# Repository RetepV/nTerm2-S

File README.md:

# nTerm2-S

> [!IMPORTANT]
> I have permanently decided to drop the CP2102 in favor of the FT231 as a USB<->Serial bridge. The CP2102 is just near impossible to solder with a soldering iron, and it was one of my objectives to not have to use hot air. As the rest of the design design is basically still the same, I decided to freeze this repository, keeping it like it is for whoever is interested, and start a new repository for the FT231 version. The design is working: if you make a board it should work, mine does.\
> \
> However, do note that I decided to move to the FT231 already before I made boards with the ESD USB protection circuit USBLC6-2SC6. It's in the latest design files here, but no boards were made and it has not been tested. However, that circuit is so uncomplicated, that I'm sure it will work fine. In worst case you can leave out the USBLC6-2SC6 and just connect pins 1-6 and 3-4. However, without ESD protection, I would suggest to connect the nTerm2-S through a cheap USB hub. No sense in jeopardising your USB ports.\
> \
> Also, I decided to add an RTC to nTerm2-S, and that's only in the FT231 version.\
> \
> Long story short, have look here for continuation of this project: https://github.com/RetepV/nTerm2-S-FT231

My rendition of the uTerm2-S by Just4Fun (https://hackaday.io/project/181583-uterm2-s-a-multi-emulation-color-rs232-terminal). This one is in SMD, and I hopefully made it easily hand-solderable for everyone (with maybe the exception of the CP2102). Obviously the 'n' in nTerm stands for 'nano.' :P

The nTerm2-S has a slightly more usable form the uTerm2-S, I think. Smaller and a little more usable when sitting permanently on a desk. And as an extra, it can switch between normal and cross (null-modem) from the software so that you wil never have to search for that null-modem cable ever again. It can also switch between RTS/CTS or DTR/DSR handshaking.

Supports RxD/TxD with RTS/CTS. Also supports DTR/DSR in a way. It is possible to switch the RTS/CTS lines to the DTR/DSR lines, using the ESP32's RTS/CTS support to manage the DTR/DSR. It's not really DTR/DSR, but as the ESP32 is a plenty fast enough DTE and only the DCE might be slow, it will work most of the times.

The nTerm2-S is ultimately based on the FABGL library and board design from Fabrizio Di Vittori. http://www.fabglib.org. However, I skipped Fabrizio's implementation and based my design on Just4Fun's uTerm2-S. https://j4f.info/uterm2-s

THIS IS A WORK IN PROGESS! I.E. UNLESS STATED AS WORKING, ASSUME THAT IT DOES NOT WORK! NO FIRMWARE HAS BEEN TESTED YET, AND AS THERE ARE SMALL DIFFERENCES IN GPIO ASSIGNMENTS, I DON'T EXPECT THE DEFAULT FABGL EXAMPLES TO WORK WITHOUT TWEAKS.

<sub><s>NOTE: The relay circuit with the bistable relays is directly out of the OMRON databook, and it allows me to switch the relay but use only power when switching (and some losses through the 470 resistor when switched on: 7mA continuous, which is a huge of a lot better than 30mA continuous when using a normal relay). That circuit sources the power from the input, which is connected to a GPIO. ESP32 GPIO pins can source 40mA and sink 28mA. According to the datasheet, the relay needs 100mW of power to switch. At 3V, that is 33mA, but we use 3.3V, so some 30mA. So when switching 'on', the ESP32 will need to source 30mA and settle at some 7mA (all theoretically, be advised). That is quite a lot, but still within spec. The ESP32 does not have to sink much, as the reverse current will go through the diode directly to ground.</s><sub>

<sub>It turned out that the ESP32 was not able to source enough power after all, so I have had to change the circuit somewhat. Now all the necessary power comes from the 5V Vbus and is switched through another transistor. I couldn't properly measure the current draw from the ESP32's GPIO port, but it looked as if it was some 4mA.</sub>

<sub>Progress! I received my fuses and did some real measurements. I used 3.3V, BAT45 (commit says 1N4148, but I was mistaken, they are BAT45's), BC337, 220u and 470 ohm on my bread board, and measured about 14mA max when switching, and 6.8mA continuous. I expected more than 14mA when switching, but maybe this relay is better than the specs? In any case, I decided to experiment with the C and R. I upped the C to 470uF, which seemed to make the switching more reliable. But more importantly, I increased the resistor in steps to see what the result would be. And found that I could go up to at least 3K9 before the switching would become unreliable. 10K was clearly too much, and I didn't try anything in between 3K9 and 10K. With 3K9, 0.88mA is drawn, and I find that good enough. The low current power led uses 3mA, and I keep that on all the time. 1mA is fine.</sub>

<sub>Created the gerbers for v0.1 and sent out to JLPCB. Jeez, it's cheap. 11 euro for 5 boards. Still had a bunch of warnings from the pins/vias of the USB-C connector and ESP32 footprints that I just could not resolve. Decided to take my chances, and JLCPCB accepted the gerbers and has actually already finished and posted the boards. So I expect the boards to be here in a few days. In the mean time, I've been doing some basic work and redesign for a version 2 of the nTerm2-S, with an SD card slot and psram, to make it more versatile (e.g. PC emulation). However, let's get this first version to work first, the objective is to have a terminal with software switchable null-modem.</sub>

<sub>After my v0.1 boards arrived I built one up. I did it in stages, starting with the CP2102 and then the power (I use the CP2102 in bus-powered mode). After much cursing, I got the CP2012 straight on the pads and it looked good under the microscope. I then added the power supply components and the USB-C port. No ESD protection yet. Doublechecked everything 10 times under the microscope, got out an old cheap USB hub (better to blow up the hub than my Macbook's port) and plugged the nTerm in. And Windows detected the CP2102 immediately, installed the drivers, and... success #1 was there!</sub>

<sub>I then added the ESP32. Could update its firmware. Success #2! Soldered the video DAC and VGA port (and fixed the ESP32). Success #3: we have video! Then populated the keyboard and mouse circuits. Success #4! After playing some Space Invaders, I populated the MAX3232 and hardwired the Rx and Tx together to do a loopback test. And we had success #5!</sub>

<sub>Then the problems started. After populating the relay circuits, I could not get them to switch. After lots of measuring and experimenting with an oscilloscope, I could only conclude that the ESP32 was simply not able to source a high enough voltage and that all my calculations and experiments apparently had been wrong. The switching voltage of the relay is 3V. But I found that the ESP32, in my setting, delivered only some 3.15V, and that goes through the BAT43W diode. The diode has a low voltage drop, but it's still something like 0.55V or more at 30mA, and that brings the operating voltage down to 2.61V. Switching one way (with a 1 on the GPIO), it means that the relay gets 2.61V, which is enough to switch it that way. But not the other way. The capacitor is charged with 2.61V. But when it discharges, it discharges through the BC817, which adds another voltage drop of somewhere between 0.1 and 0.4 volt. And now, with worst case 2.21V we are just around the minimum set voltage for the relay, which is 2.25V typical. The charge in the capacitor is not enough to deliver enough energy in that case.</sub>

<sub>So now I had to experiment with the board itself and found that what I could do was to change the input diode to a transistor in common collector (emitter follower) configuration, and basically buffer ESP32's GPIO. So I replaced the BAT43 diode with a BC817 transistor, with collector tied to 5V and emitter tied to the input of the circuit. This brings the voltage into the circuit up to the 3.15V that the ESP32 was outputting (voltage drop of the transistor is negated by feeding it 5V). And after fiddling a bit with resistor and capacitor values I got it all working reliably.</sub>

<sub>I left it at that, it was working now with minimal changes and no inrease in cost.</sub>

<sub>Problems encountered and fixed:</sub>

<sub>1. The CP2102 was really hard to solder, even using hot air. I am looking into the FT231 as a much easier to solder alternative. But the FT231 seems to have more driver issues than the CP2102 (which has none, as far as I know). As an alternative, it might help to increase the size of the pads.
2. The ESD protection diodes were much tinier than I thought. Looking at the PCB in Kicad, they didn't seem so small. :) So I should try to find larger diodes.
3. I thought I had an ESP32 lying around, but it turned out that I only had one that was soldered to a breakout board. So I decided to desolder that, instead of wait for new ones to arrive. Well, that did not go too well. I ripped off one of the castellated pads, one which is used for hSync. So no video. But I a not defeated so easily, so I lifted the cap off the module, soldered a wire directly to the ESP32 chip and ran it to the HSYNC line. Win! .;) I could start some serious testing
4. The relay circuits don't work. Had to redesign somewhat.
5. I accidentally used the J-leg footprint for the IM41's instead of the Gullwing footprint.
6. Many of the large capacitor's footprints were simply wrong and I had to solder one vertically.
7. I used tantalum caps in the relay circuits, but there's no reason to not use the much cheaper normal electrolytic caps.
</sub>

<sub>After a fixing all of the above, and refactoring a few things on the board, version v0.6 was arrived at. And once again I had boards made by JCPCB. 17 euro for 5 boards. Still cheap, but no discount for me this time. The new boards arrived in record time, and I went to populate one.<s/ub>

<sub>Observations:</sub>

<sub>1. Still have one capacitor's footprint wrong. Although this I was able to fit it horizontally at least.
2. CP2102 solders much easier with the larger sized pads. But it still is fiddly to hand-solder a QFN-28 chip. I wish Silicon Labs would make a QFP-28 version.
3. The board is detected by my Macbook, but can't communicate with it. My Windows machine is luckily able to communicate and flash, but it doesn't seem too happy about it all. What's going on? Turns out that I had chosen ESD diodes for their size, but did not realize that with their size also comes a high capacity of some 100pF. And that's enough to mess up the USB communications. So it's back to the ol' drawing board here. Removing the ESD diodes makes USB work again on all my machines. But i want them, so we'll need a new revision already. 
4. My new relay circuits work! Flawlessly even!
5. Why did I not add an option to keep the amplifier circuit unpopulated and have a line-out instead of a speaker-out? Or why not both options, selectable throguh solder bridges?</sub>

<sub>Apart from these issues, nTerm2-S v0.5 works!</sub>

<sub>v0.1 vs v0.5:</sub>

<sub>Testing v0.5</sub>

<sub>I just finished the v0.6 design with fixes for all of the above. That would be the final design, with only a slight feature creep (being able to omit/bypass the speaker amplifier). Now we need software...</sub>

This design is available under GPL License V3. This means that I DO NOT release it for commercial use, unless with my explicit written and signed consent. Please contact me if you have commercial questions.

uTerm2-S: https://hackaday.io/project/181583-uterm2-s-a-multi-emulation-color-rs232-terminal  
fabgl: http://www.fabglib.org/, https://github.com/fdivitto/FabGL

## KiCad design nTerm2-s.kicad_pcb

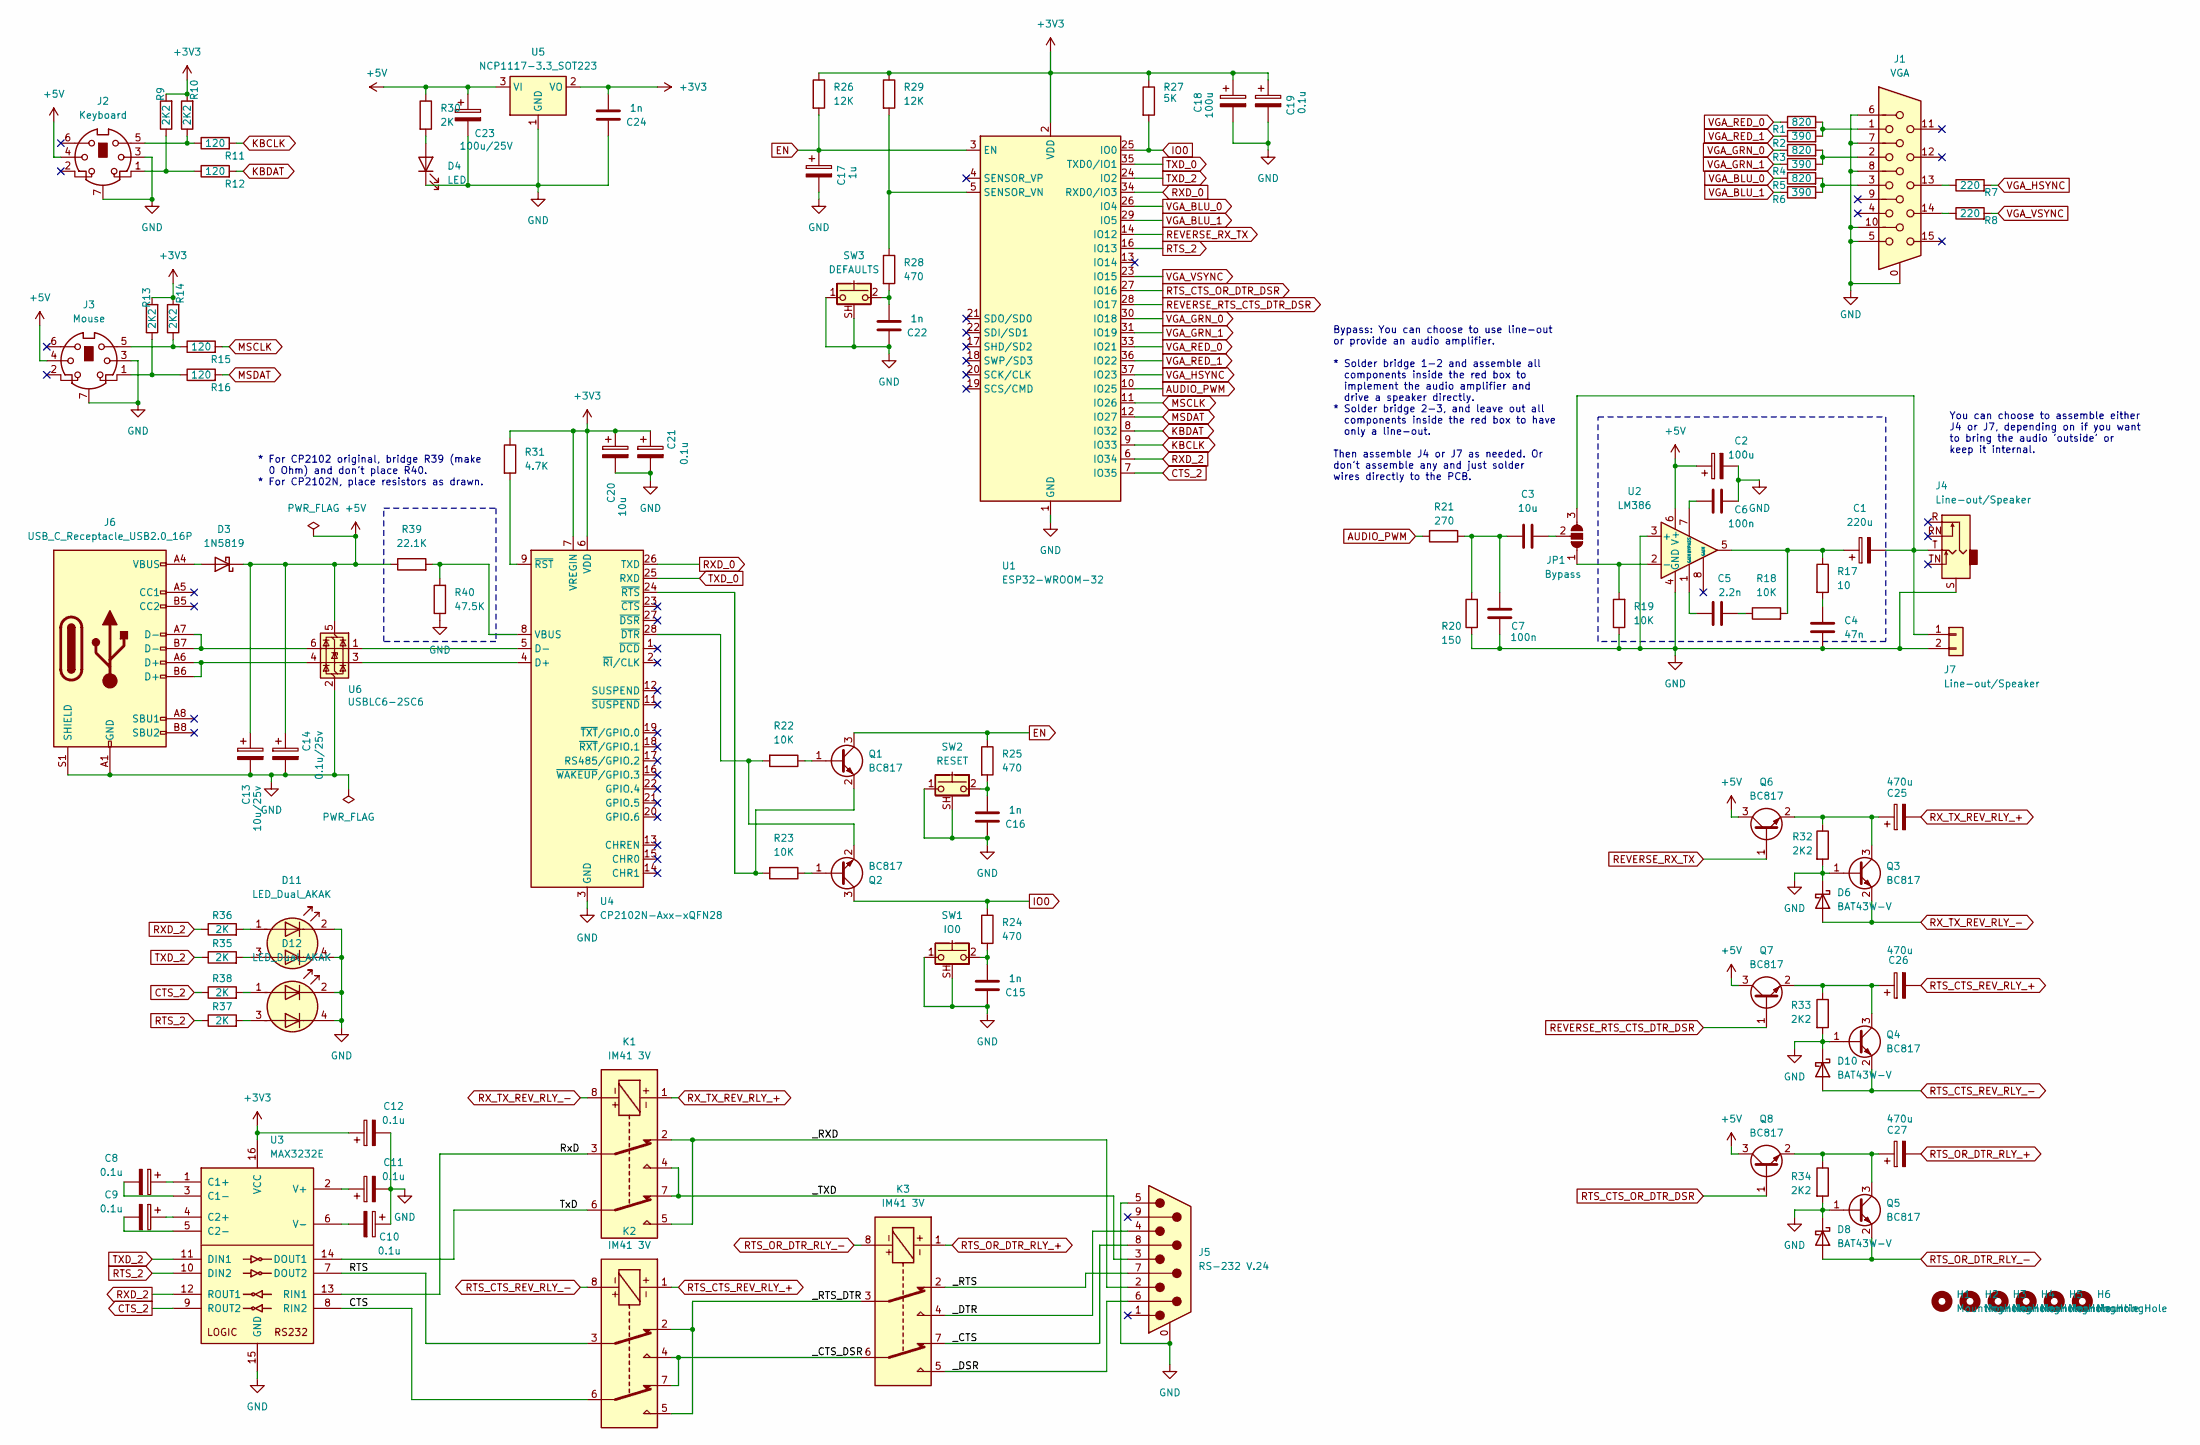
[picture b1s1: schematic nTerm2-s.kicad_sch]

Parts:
C1: 220u; CP_Elec_6.3x7.7
C2: 100u; CP_Elec_6.3x7.7
C3: 10u; C_0805_2012Metric_Pad1.18x1.45mm_HandSolder
C4: 47n; C_0603_1608Metric_Pad1.08x0.95mm_HandSolder
C5: 2.2n; C_0603_1608Metric_Pad1.08x0.95mm_HandSolder
C6, C7: 100n; C_0603_1608Metric_Pad1.08x0.95mm_HandSolder
C8, C9, C10, C11, C12, C19, C21: 0.1u; CP_EIA-3216-18_Kemet-A_Pad1.58x1.35mm_HandSolder
C13: 10u/25v; CP_EIA-6032-28_Kemet-C_Pad2.25x2.35mm_HandSolder
C14: 0.1u/25v; CP_EIA-3216-18_Kemet-A_Pad1.58x1.35mm_HandSolder
C15, C16, C22, C24: 1n; C_0603_1608Metric_Pad1.08x0.95mm_HandSolder
C17: 1u; CP_EIA-3216-18_Kemet-A_Pad1.58x1.35mm_HandSolder
C18: 100u; CP_EIA-6032-28_Kemet-C_Pad2.25x2.35mm_HandSolder
C20: 10u; CP_EIA-3528-21_Kemet-B_Pad1.50x2.35mm_HandSolder
C23: 100u/25V; CP_EIA-7343-30_AVX-N_Pad2.25x2.55mm_HandSolder
C25, C26, C27: 470u; CP_Elec_6.3x7.7
D3: 1N5819; Nexperia_CFP3_SOD-123W
D4: LED; DIALIGHT_LED_3MM_SINGLE
D6, D8, D10: BAT43W-V; D_SOD-123
D11, D12: LED_Dual_AKAK; DIALIGHT_LED_3MM_DOUBLE
H1, H2, H3, H4, H5, H6: MountingHole; MountingHole_3.2mm_M3
J1: VGA; DSUB-15-HD_Female_Horizontal_P2.29x1.98mm_EdgePinOffset3.03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
J2: Keyboard; Connector_Mini-DIN_Female_6Pin_2rows
J3: Mouse; Connector_Mini-DIN_Female_6Pin_2rows
J4: Line-out/Speaker; Jack_3.5mm_Ledino_KB3SPRS_Horizontal-alt
J5: RS-232 V.24; DSUB-9_Male_Horizontal_P2.77x2.84mm_EdgePinOffset4.94mm_Hou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
J6: USB_C_Receptacle_USB2.0_16P; USB_C_Receptacle_Molex_213716-0001
J7: Line-out/Speaker; PinHeader_1x02_P2.54mm_Vertical
JP1: Bypass; SolderJumper-3_P1.3mm_Open_RoundedPad1.0x1.5mm_NumberLabels
K1, K2, K3: IM41 3V; Relay_DPDT_AXICOM_IMSeries_Gullwing
Q1, Q2, Q3, Q4, Q5, Q6, Q7, Q8: BC817; SOT-23
R1, R3, R5: 820; R_0603_1608Metric_Pad0.98x0.95mm_HandSolder
R2, R4, R6: 390; R_0603_1608Metric_Pad0.98x0.95mm_HandSolder
R7, R8: 220; R_0603_1608Metric_Pad0.98x0.95mm_HandSolder
R9, R10, R13, R14, R32, R33, R34: 2K2; R_0603_1608Metric_Pad0.98x0.95mm_HandSolder
R11, R12, R15, R16: 120; R_0603_1608Metric_Pad0.98x0.95mm_HandSolder
R17: 10; R_0603_1608Metric_Pad0.98x0.95mm_HandSolder
R18, R19, R22, R23: 10K; R_0603_1608Metric_Pad0.98x0.95mm_HandSolder
R20: 150; R_0603_1608Metric_Pad0.98x0.95mm_HandSolder
R21: 270; R_0603_1608Metric_Pad0.98x0.95mm_HandSolder
R24, R25, R28: 470; R_0603_1608Metric_Pad0.98x0.95mm_HandSolder
R26, R29: 12K; R_0603_1608Metric_Pad0.98x0.95mm_HandSolder
R27: 5K; R_0603_1608Metric_Pad0.98x0.95mm_HandSolder
R30, R35, R36, R37, R38: 2K; R_0603_1608Metric_Pad0.98x0.95mm_HandSolder
R31: 4.7K; R_0603_1608Metric_Pad0.98x0.95mm_HandSolder
R39: 22.1K; R_0603_1608Metric_Pad0.98x0.95mm_HandSolder
R40: 47.5K; R_0603_1608Metric_Pad0.98x0.95mm_HandSolder
SW1: IO0; SW_Tactile_SPST_Angled_PTS645Vx58-2LFS-alt
SW2: RESET; SW_Tactile_SPST_Angled_PTS645Vx58-2LFS-alt
SW3: DEFAULTS; SW_Tactile_SPST_Angled_PTS645Vx58-2LFS-alt
U1: ESP32-WROOM-32
U2: LM386; SOIC-8_3.9x4.9mm_P1.27mm
U3: MAX3232E; SOIC-16_3.9x9.9mm_P1.27mm
U4: CP2102N-Axx-xQFN28; QFN-28-1EP_5x5mm_P0.5mm_EP3.35x3.35mm_handsolder
U5: NCP1117-3.3_SOT223; SOT-223-3_TabPin2
U6: USBLC6-2SC6; SOT-23-6

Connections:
+3V3: C12.1, C18.1, C19.1, C20.1, C21.1, C24.1, R9.2, R10.2, R13.2, R14.2, R26.1, R27.1, R29.1, R31.1, U1.2 (VDD), U3.16 (VCC), U4.6 (VDD), U4.7 (VREGIN), U5.2 (VO)
+5V: C2.1, C13.1, C14.1, C23.1, D3.1 (K), J2.4, J3.4, Q6.3 (C), Q7.3 (C), Q8.3 (C), R30.1, R39.1, U2.6 (V+), U5.3 (VI), U6.5 (VBUS)
/CTS: K2.6, U3.8 (RIN2)
/RTS: K2.3, U3.7 (DOUT2)
/RxD: K1.3, U3.13 (RIN1)
/TxD: K1.6, U3.14 (DOUT1)
/_CTS: J5.8, K3.7
/_CTS_DSR: K2.4, K2.7, K3.6
/_DSR: J5.6, K3.5
/_DTR: J5.4, K3.4
/_RTS: J5.7, K3.2
/_RTS_DTR: K2.2, K2.5, K3.3
/_RXD: J5.2, K1.2, K1.5
/_TXD: J5.3, K1.4, K1.7
AUDIO_PWM: R21.2, U1.10 (IO25)
CTS_2: R38.1, U1.7 (IO35), U3.9 (ROUT2)
EN: C17.1, Q1.3 (C), R25.1, R26.2, U1.3 (EN)
GND: C2.2, C4.2, C6.2, C7.1, C10.1, C11.2, C12.2, C13.2, C14.2, C15.2, C16.2, C17.2, C18.2, C19.2, C20.2, C21.2, C22.2, C23.2, C24.2, D4.2 (K), D6.1 (K), D8.1 (K), D10.1 (K), D11.2 (K1), D11.4 (K2), D12.2 (K1), D12.4 (K2), J1.0, J1.5, J1.6, J1.7, J1.8, J1.10, J2.3, J2.7, J3.3, J3.7, J4.S, J5.0 (PAD), J5.5, J6.A1 (GND), J6.A12 (GND), J6.B1 (GND), J6.B12 (GND), J6.S1 (SHIELD), J7.2, Q3.1 (B), Q4.1 (B), Q5.1 (B), R19.1, R20.1, R32.2, R33.2, R34.2, R40.1, SW1.1, SW1.SH (B), SW2.1, SW2.SH (B), SW3.1, SW3.SH (B), U1.1 (GND), U1.15 (GND), U1.38 (GND), U1.39 (GND), U2.3 (+), U2.4 (GND), U3.15 (GND), U4.3 (GND), U4.29 (GND), U5.1 (GND), U6.2 (GND)
IO0: Q2.3 (C), R24.1, R27.2, U1.25 (IO0)
KBCLK: R11.2, U1.9 (IO33)
KBDAT: R12.2, U1.8 (IO32)
MSCLK: R15.2, U1.11 (IO26)
MSDAT: R16.2, U1.12 (IO27)
unnamed: C1.1, R17.1, R18.2, U2.5
unnamed: C3.1, C7.2, R20.2, R21.1
unnamed: C4.1, R17.2
unnamed: C5.1, U2.1 (GAIN)
unnamed: C5.2, R18.1
unnamed: C15.1, R24.2, SW1.2
unnamed: C16.1, R25.2, SW2.2
unnamed: C22.1, R28.2, SW3.2
unnamed: D3.2 (A), J6.A4 (VBUS), J6.A9 (VBUS), J6.B4 (VBUS), J6.B9 (VBUS)
unnamed: D4.1 (A), R30.2
unnamed: D11.1 (A1), R36.2
unnamed: D11.3 (A2), R35.2
unnamed: D12.1 (A1), R38.2
unnamed: D12.3 (A2), R37.2
unnamed: J1.1, R1.2, R2.2
unnamed: J1.2, R3.2, R4.2
unnamed: J1.3, R5.2, R6.2
unnamed: J1.13, R7.1
unnamed: J1.14, R8.1
unnamed: J2.1, R9.1, R12.1
unnamed: J2.5, R10.1, R11.1
unnamed: J3.1, R13.1, R16.1
unnamed: J3.5, R14.1, R15.1
unnamed: J6.A6 (D+), J6.B6 (D+), U6.4 (I/O2)
unnamed: J6.A7 (D-), J6.B7 (D-), U6.6 (I/O1)
unnamed: C1.2, J4.T, J7.1, JP1.3 (B)
unnamed: JP1.1 (A), R19.2, U2.2 (-)
unnamed: C3.2, JP1.2 (C)
unnamed: Q1.1 (B), R22.1
unnamed: Q1.2 (E), R23.2, U4.24 (~RTS)
unnamed: Q2.1 (B), R23.1
unnamed: Q2.2 (E), R22.2, U4.28 (~DTR)
unnamed: C25.1, Q3.3 (C), Q6.2 (E), R32.1
unnamed: C26.1, Q4.3 (C), Q7.2 (E), R33.1
unnamed: C27.1, Q5.3 (C), Q8.2 (E), R34.1
unnamed: R28.1, R29.2, U1.5 (SENSOR_VN)
unnamed: C6.1, U2.7 (BYPASS)
unnamed: C8.1, U3.1 (C1+)
unnamed: C8.2, U3.3 (C1-)
unnamed: C9.1, U3.4 (C2+)
unnamed: C9.2, U3.5 (C2-)
unnamed: C11.1, U3.2 (V+)
unnamed: C10.2, U3.6 (V-)
unnamed: U4.4 (D+), U6.3 (I/O2)
unnamed: U4.5 (D-), U6.1 (I/O1)
unnamed: R39.2, R40.2, U4.8 (VBUS)
unnamed: R31.2, U4.9 (~RST)
REVERSE_RTS_CTS_DTR_DSR: Q7.1 (B), U1.28 (IO17)
REVERSE_RX_TX: Q6.1 (B), U1.14 (IO12)
RTS_2: R37.1, U1.16 (IO13), U3.10 (DIN2)
RTS_CTS_OR_DTR_DSR: Q8.1 (B), U1.27 (IO16)
RTS_CTS_REV_RLY_+: C26.2, K2.1
RTS_CTS_REV_RLY_-: D10.2 (A), K2.8, Q4.2 (E)
RTS_OR_DTR_RLY_+: C27.2, K3.1
RTS_OR_DTR_RLY_-: D8.2 (A), K3.8, Q5.2 (E)
RXD_0: U1.34 (RXD0/IO3), U4.26 (TXD)
RXD_2: R36.1, U1.6 (IO34), U3.12 (ROUT1)
RX_TX_REV_RLY_+: C25.2, K1.1
RX_TX_REV_RLY_-: D6.2 (A), K1.8, Q3.2 (E)
TXD_0: U1.35 (TXD0/IO1), U4.25 (RXD)
TXD_2: R35.1, U1.24 (IO2), U3.11 (DIN1)
VGA_BLU_0: R5.1, U1.26 (IO4)
VGA_BLU_1: R6.1, U1.29 (IO5)
VGA_GRN_0: R3.1, U1.30 (IO18)
VGA_GRN_1: R4.1, U1.31 (IO19)
VGA_HSYNC: R7.2, U1.37 (IO23)
VGA_RED_0: R1.1, U1.33 (IO21)
VGA_RED_1: R2.1, U1.36 (IO22)
VGA_VSYNC: R8.2, U1.23 (IO15)

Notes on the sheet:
You can choose to assemble either J4 or J7, depending on if you want to bring the audio 'outside' or keep it internal.
* For CP2102 original, bridge R39 (make 0 Ohm) and don't place R40. * For CP2102N, place resistors as drawn.
Bypass: You can choose to use line-out or provide an audio amplifier. * Solder bridge 1-2 and assemble all components inside the red box to implement the audio amplifier and drive a speaker directly. * Solder bridge 2-3, and leave out all components inside the red box to have only a line-out. Then 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

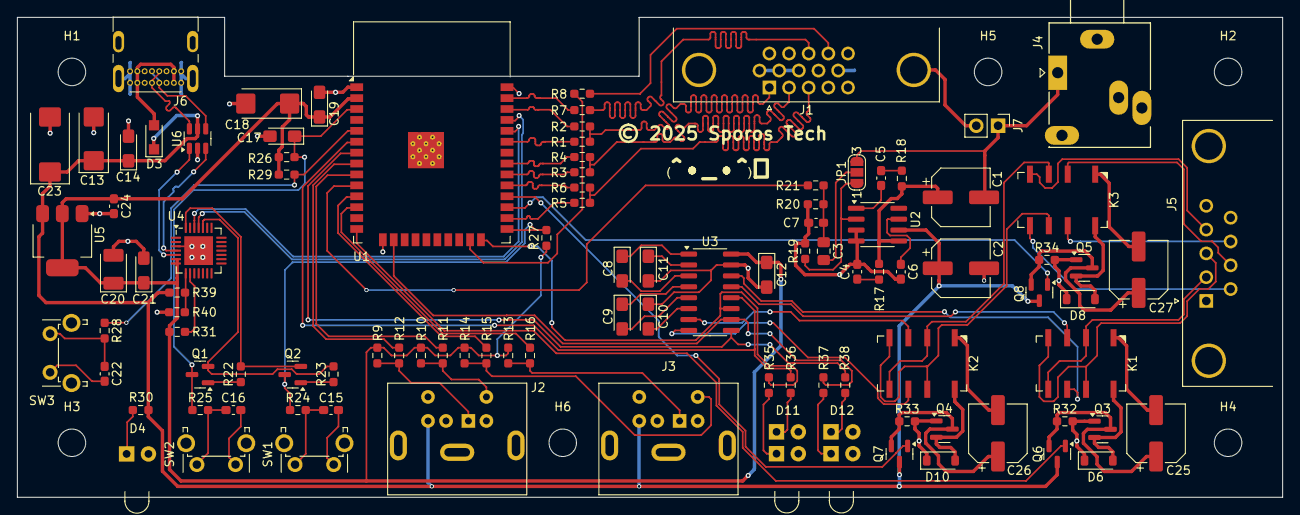
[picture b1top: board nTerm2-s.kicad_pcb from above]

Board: 2 copper layers, 147.3 x 55.9 mm, 108 parts (0 on the bottom side), 92 nets.

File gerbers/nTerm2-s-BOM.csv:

"Id";"Designator";"Footprint";"Quantity";"Designation";"Supplier and ref";
1;"R28,R25,R24";"R_0603_1608Metric_Pad0.98x0.95mm_HandSolder";3;"470";;;
2;"R2,R4,R6";"R_0603_1608Metric_Pad0.98x0.95mm_HandSolder";3;"390";;;
3;"R26,R29";"R_0603_1608Metric_Pad0.98x0.95mm_HandSolder";2;"12K";;;
4;"R33,R34,R32";"R_0603_1608Metric_Pad0.98x0.95mm_HandSolder";3;"3K9";;;
5;"R18,R22,R23,R19";"R_0603_1608Metric_Pad0.98x0.95mm_HandSolder";4;"10K";;;
6;"D1,D2";"D_SMA";2;"P4SMAJ5.0CA";;;
7;"D7,D10,D5,D9,D6,D8";"D_SOD-123";6;"BAT43W-V";;;
8;"K1,K2,K3";"Relay_DPDT_AXICOM_IMSeries_Gullwing";3;"IM41 3V";;;
9;"SW2";"SW_Tactile_SPST_Angled_PTS645Vx58-2LFS";1;"RESET";;;
10;"R17";"R_0603_1608Metric_Pad0.98x0.95mm_HandSolder";1;"10";;;
11;"U1";"ESP32-WROOM-32";1;"ESP32-WROOM-32";;;
12;"R14,R9,R13,R10";"R_0603_1608Metric_Pad0.98x0.95mm_HandSolder";4;"2K2";;;
13;"SW1";"SW_Tactile_SPST_Angled_PTS645Vx58-2LFS";1;"IO0";;;
14;"C6,C7";"C_0603_1608Metric_Pad1.08x0.95mm_HandSolder";2;"100n";;;
15;"J2";"Connector_Mini-DIN_Female_6Pin_2rows";1;"Keyboard";;;
16;"C25,C26,C27";"CP_Elec_6.3x7.7";3;"470u";;;
17;"D11,D12";"DIALIGHT_LED_3MM_DOUBLE";2;"LED_Dual_AKAK";;;
18;"R38,R37,R36,R35,R30";"R_0603_1608Metric_Pad0.98x0.95mm_HandSolder";5;"2K";;;
19;"U2";"SOIC-8_3.9x4.9mm_P1.27mm";1;"LM386";;;
20;"R8,R7";"R_0603_1608Metric_Pad0.98x0.95mm_HandSolder";2;"220";;;
21;"C24,C16,C15,C22";"C_0603_1608Metric_Pad1.08x0.95mm_HandSolder";4;"1n";;;
22;"R12,R15,R16,R11";"R_0603_1608Metric_Pad0.98x0.95mm_HandSolder";4;"120";;;
23;"C10,C9,C21,C12,C8,C11,C19";"CP_EIA-3216-18_Kemet-A_Pad1.58x1.35mm_HandSolder";7;"0.1u";;;
24;"C14";"CP_EIA-3216-18_Kemet-A_Pad1.58x1.35mm_HandSolder";1;"0.1u/25v";;;
25;"J3";"Connector_Mini-DIN_Female_6Pin_2rows";1;"Mouse";;;
26;"U5";"SOT-223-3_TabPin2";1;"NCP1117-3.3_SOT223";;;
27;"C18";"CP_EIA-6032-28_Kemet-C_Pad2.25x2.35mm_HandSolder";1;"100u";;;
28;"R20";"R_0603_1608Metric_Pad0.98x0.95mm_HandSolder";1;"150";;;
29;"U3";"SOIC-16_3.9x9.9mm_P1.27mm";1;"MAX3232E";;;
30;"C23";"CP_EIA-6032-28_Kemet-C_Pad2.25x2.35mm_HandSolder";1;"100u/25V";;;
31;"Q5,Q2,Q1,Q3,Q4";"SOT-23";5;"BC817";;;
32;"R39";"R_0603_1608Metric_Pad0.98x0.95mm_HandSolder";1;"22.1K";;;
33;"J6";"USB_C_Receptacle_Molex_213716-0001";1;"USB_C_Receptacle_USB2.0_16P";;;
34;"C20";"CP_EIA-3528-21_Kemet-B_Pad1.50x2.35mm_HandSolder";1;"10u";;;
35;"SW3";"SW_Tactile_SPST_Angled_PTS645Vx58-2LFS";1;"DEFAULTS";;;
36;"C5";"C_0603_1608Metric_Pad1.08x0.95mm_HandSolder";1;"2.2n";;;
37;"R5,R3,R1";"R_0603_1608Metric_Pad0.98x0.95mm_HandSolder";3;"820";;;
38;"D4";"DIALIGHT_LED_3MM_SINGLE";1;"LED";;;
39;"J5";"DSUB-9_Male_Horizontal_P2.77x2.84mm_EdgePinOffset4.94mm_Housed_MountingHolesOffset7.48mm";1;"DE9_Plug_MountingHoles";;;
40;"C2";"CP_Elec_6.3x7.7";1;"100u";;;
41;"C1";"CP_Elec_6.3x7.7";1;"220u";;;
42;"U4";"QFN-28-1EP_5x5mm_P0.5mm_EP3.35x3.35mm";1;"CP2102N-Axx-xQFN28";;;
43;"J1";"DSUB-15-HD_Female_Horizontal_P2.29x1.98mm_EdgePinOffset8.35mm_Housed_MountingHolesOffset10.89mm";1;"VGA";;;
44;"R21";"R_0603_1608Metric_Pad0.98x0.95mm_HandSolder";1;"270";;;
45;"C3";"C_0805_2012Metric_Pad1.18x1.45mm_HandSolder";1;"10u";;;
46;"J4";"Jack_3.5mm_Ledino_KB3SPRS_Horizontal";1;"Speaker";;;
47;"C4";"C_0603_1608Metric_Pad1.08x0.95mm_HandSolder";1;"47n";;;
48;"C13";"CP_EIA-6032-28_Kemet-C_Pad2.25x2.35mm_HandSolder";1;"10u/25v";;;
49;"R27";"R_0603_1608Metric_Pad0.98x0.95mm_HandSolder";1;"5K";;;
50;"R40";"R_0603_1608Metric_Pad0.98x0.95mm_HandSolder";1;"47.5K";;;
51;"R31";"R_0603_1608Metric_Pad0.98x0.95mm_HandSolder";1;"4.7K";;;
52;"D3";"Nexperia_CFP3_SOD-123W";1;"1N5819";;;
53;"C17";"CP_EIA-3216-18_Kemet-A_Pad1.58x1.35mm_HandSolder";1;"1u";;;

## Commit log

2025-01-15 Initial WIP commit.
2025-01-17 Improvements: - Move 'defaults' button to side, to create space for extra mounting holes. - Change type of USB pug to one with through-hole mounts for extra strength. - Fix audio plug. - Keep some di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
2025-01-17 Add PDF of schematic for easier viewing.
2025-01-19 Made board smaller for easier fitting in enclosure (150x55 or so). Many fixes. All vias are on 1.27 grid. USB-C ocnnector. VGA signal lines all same length, hopefully helping to give good video outpu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
2025-01-20 Some backups
2025-01-20 Backup
2025-01-24 * Final details sorted. Hopefully I've got it all now. * Generated gerbers and sent to JLCPCB for boards to be made. * Fuses for my Fluke 175 multimeter arrived. Experimented with the relay driving c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
2025-01-24 Some backups.
2025-01-29 Update wrong footprint for relays K1..K3.
2025-01-29 Fix all tantalum capacitor sizes.
2025-01-29 Some small replacements, doublechecked size of tiny ESD protectors, but they are really *tiny*. Set them further apart, so maybe they are easier to solder this way.
2025-01-29 Use other TVS protection diodes, with a hand-solderable size.
2025-02-04 More small improvements to layout.
2025-02-19 v0.04
2025-02-24 nTerm2-S v0.05 - New PCBs ordered.
2025-03-11 Fix some small things (Forgot to update version in the .sch file). Create PDFs. Update a few backups.
2025-03-17 V0.06 - Use USBLC6-2 for ESD protection, instead of those big TVS diodes. Those big TVS diodes were a bad choice, they have far too high a capacity for USB 2.0 use. Removed resistors from the bases o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
2025-03-17 Update capacitor footprint to larger size.
2025-03-18 Hide the silk screen Hx designations of the mounting holes... :)
2025-03-23 Another backup.
2025-05-21 Some small updates, a fix, and exported all libraries into the project, for distribution.
2025-05-21 New backup was created.
2026-04-30 Revise troubleshooting section for relay circuit issues
    Clarified issues with relay circuits and ESP32 voltage sourcing. Updated troubleshooting steps and solutions for better reliability.
2026-04-30 Revise relay circuit explanation and solutions
    Clarified issues with relay circuit and voltage drops. Updated solution details for using a BC817 transistor to improve circuit performance.
2026-04-30 Revise README with circuit modification details
    Updated the explanation of the circuit modifications made to improve relay switching performance, including details on replacing the BAT43 diode with a BC817 transistor and the resulting voltage chan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
2026-04-30 Fix typo in README about cost
    Corrected a minor typographical error in the README regarding the phrase 'no inrease in cost'.
2026-04-30 Fix repeated content and clarify relay circuit troubleshooting
    Corrected repeated sections and improved clarity on the relay circuit issues and solutions.

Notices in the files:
nTerm2-s.kicad_pcb:
© 2025 Sporos Tech ₍^•_•^₎ﾉ
